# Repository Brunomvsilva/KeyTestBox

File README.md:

# KeytestBox

_Embedded platform designed to integrate automotive HMI key-testing systems in production environments._

_This project was developed at Preh Portugal as part of my Master’s thesis._

---

## Preview

<table align="center">
  <tr>
    <td align="center">
      <br>
      <em>Real KeytestBox Image</em>
    </td>
    <td align="center">
      <br>
      <em>3D model of the KeyTestBox enclosure</em>
    </td>
  </tr>
</table>

---

## Table of Contents

- [Introduction](#introduction)
- [Typical Key Test Output](#typical-key-test-output)
- [Incremental vs Continuous Tests](#incremental-vs-continuous-tests)
  - [Incremental Tests](#incremental-tests)
  - [Continuous Tests](#continuous-tests)
- [Problem Statement](#problem-statement)
  - [Problem 1: Delay via CAN/LIN](#problem-1-delay-when-reading-uut-data-via-can-or-lin)
  - [Problem 2: Low resolution and missed events](#problem-2-low-resolution-and-missed-events-in-incremental-tests)
  - [Consequence](#consequence-forced-to-use-expensive-continuous-test-systems)
- [Solution, Main Goals and Requirements](#solution-main-goals-and-requirements)
  - [Main Goals](#main-goals)
  - [Hardware Requirements](#hardware-requirements)
  - [Software Requirements](#software-requirements)
- [Hardware Overview](#hardware-overview)
- [Final Hardware](#final-hardware)
- [Software and Tools Used](#software-and-tools-used)
- [MQTT Commands Implemented](#mqtt-commands-implemented)
- [Tests and Results](#tests-and-results)
  - [UUT Lever and Testbench Setup](#uut-lever-test-and-testbench-setup)
  - [Sampling and Performance](#sampling-and-performance)
- [Conclusion](#conclusion)
- [Skills Learned](#skills-learned)

---

## Introduction 

Automotive HMI, such as climate and central control panels, rely on high-quality tactile feedback. **Force–displacement** key tests quantify that feel essencially by measuring the relation between **applied force** and **key travel**.

Images below display the **main components** of a key test system

<div align="center">
<table>
  <tr>
    <td style="padding-right: 40px;">
      
    </td>
    <td style="padding-left: 40px;">
      
    </td>
  </tr>
</table>
</div>

### During a test:
- The key is pressed by a **SMAC linear motor**  
- **Force** is measured using a **load cell with an amplifier**  
- **Key travel (displacement)** is obtained from the **SMAC internal encoder**  
- The **Unit Under Test (UUT)** sends data via **CAN/LIN** during the test, such as:  
  - **Key state (pressed / released)**
  - **Lever position or angle** (e.g. gear selector tests)  
  - **Selected gear value**  
  - **UUT Hall sensors or internal position data**  
  - Other diagnostic or status information

### Typical Key Test Output

The **Force–Displacement** curve is the most common way to characterize how a key or button behaves when it is pressed and released. It represents the force applied to the key as a function of its travel (displacement).

Curves differ depending on the type of key being tested.
During a test, the key is pressed (force increases) until it reaches a maximum point, and then released. From this curve, mechanical parameters of the key can be extracted:

| Symbol | Description |
|--------|-------------|
| **S1** | Displacement at which the key actuates (snap/collapse point). |
| **F1** | Actuation force – force required to trigger the snap of the membrane or key mechanism at S1. |
| **S2** | Displacement where electrical contact occurs with the PCB. |
| **F2** | Contact force – minimum force required to close the electrical contact at S2. |
| **F3** | Return force – force at which the electrical contact is released during the return movement. |
| **F4** | Force difference between actuation and release states. |
| **F5** | Maximum applied force during the test (should not exceed mechanical limits). |
| **Ss** | Maximum travel / end of mechanical stroke. |

One of the most important metrics derived from this curve is the **Snap Ratio (SR)**, which indicates how strong the tactile feedback is:

$$
SR=\dfrac{F_1-F_2}{F_1}\times 100\%
$$

- A higher **Snap Ratio** = stronger tactile feedback (more noticeable “click”).
- A lower **Snap Ratio** = softer feedback, which may feel smoother but less perceptible.
- Ideal **SR** values depend on the application.

---

## Incremental vs Continuous Tests

The flowcharts below provide a simplified comparison between the two testing methods.  
The main difference is that in **Incremental Tests**, the actuator stops at each step to acquire a sample, while in **Continuous Tests**, the actuator moves without stopping and data is sampled in real time.

<table align="center">
  <tr>
    <td align="center">
      <br>
      <em>Incremental Test Flowchart</em>
    </td>
    <td align="center">
      <br>
      <em>Continuous Test Flowchart</em>
    </td>
  </tr>
</table>

---

## Incremental Tests

### Incremental Test System Example (without the KeyTestBox)

- **Force** data is acquired by the host PC via a USB Data Acquisition (DAQ) device from National Instruments.
- **Position** data is acquired by RS232 from the actuator controller
- **Key State or info** data is acquired through a CAN/LIN-USB converter

### Advantages:
- Low cost
- Easier to implement

### Disadvantages
- **low test resolution** (low sample density)
- May miss the sampling of the **snap point**, especially on **short-travel keys**
- Can fail to meet client requirements

### Incremental Test Output Example

---

## Continuous Tests

### Continuous Test System (Without KeyTestBox)

In continuous testing, the actuator **moves without stopping**, and all signals are sampled in real time. This enables a smoother force–displacement curve and higher data accuracy.

- **Force** is measured by a load cell and continuously acquired via the DAQ system  
- **Position (travel)** is obtained from the SMAC actuator encoder in real time  
- The **Unit Under Test (UUT)** transmits its state (CAN/LIN), such as key/lever status or sensor values, during movement  
- All data is timestamped and saved by the DAQ system for later processing  

> While this setup delivers high accuracy and resolution, it uses sophisticated hardware and is **significantly more expensive**.

### Advantages
- **High sample density** → more precise force–travel curve  
- **Accurate snap detection**  
- **Faster test execution** → important in industrial production environments  

### Disadvantages
- **Substantially higher cost** due to DAQ modules and synchronization hardware.

### Continuous Test Output Example

---

## Problem Statement

In industrial test setups, especially for testing mechanical keys, the most common approach is the **incremental test method**. This approach is simple and cost-effective, and it can work well in many cases.

However, **in several real-world situations, incremental testing is not sufficient or may not work at all**. These limitations arise due to the way the test equipment communicates and the type of measurements required:

---

### Problem 1: Delay when reading UUT data via CAN or LIN

Many devices under test (UUTs) only report their internal state (e.g., whether a button is pressed or not) when the host explicitly **requests the data** using a communication protocol like **CAN** or **LIN**. This process introduces a delay between the request and the response.

If the actuator is moving during this time (as in a continuous test), by the time the host receives the data, the key is already in a **different position**, and the measured force has also changed. This causes a mismatch between the **key state**, **position**, and **force**, making the data unreliable.

---

### Problem 2: Low resolution and missed events in incremental tests

Given the problem 1, a good solution would be to **stop the actuator** and only then **request the data via CAN or LIN**, then wait for the response.  
However, as said before, **incremental testing has limited resolution**. Since the actuator only samples at discrete steps, fast or short events — such as the **snap point** (a sudden change in force when pressing a key) — may occur between two sample points and go undetected.

This is particularly problematic for **short-travel keys**, where the full keypress happens in a very small movement range. In such cases, a small number of samples is not enough to capture the key’s behavior accurately.

---

### Consequence: Forced to use expensive continuous test systems

To solve these problems, test stations often switch to **continuous testing**, which are significantly more expensive

---

## Solution, Main Goals and Requirements

To overcome the limitations of incremental testing and avoid the high cost of commercial continuous testing systems, a new solution is required — one that enables **real-time, synchronized testing** without the complexity and price of traditional DAQ systems.

The **KeyTestBox** is proposed as a **low-cost**, **modular**, and **reusable** platform suitable for production testing environments.

### Main Goals 

- **Real-time acquisition** of:
  - **Force** (via load cell)
  - **Position** (via SMAC encoder)
  - **UUT data** (via CAN or LIN protocols)

### Hardware Requirements

- 24 VDC power supply  
- CAN interface (supports baud rate up to 1 Mbps)  
- LIN interface (supports baud rate up to 19 200 bps)  
- Ethernet port (10/100 Mbps)  
- Two RS232 interfaces  
- Minimum of five differential analog inputs (−10 V to +10 V) **(Mainly to read the 2 Load Cells but some extra were added)**  
- Two linear encoder counters  
- Microcontroller-based system
- PCB design

---

### Software Requirements

- Firmware developed in C
- Start and stop a test routine upon request  
- Ability to export the acquired test data  
- Capability to execute external commands during the test routine  
- Use of the MQTT protocol for communication with the host  

---

## Hardware Overview

---

## Final Hardware

[Full **Hardware Schematic**](PCB/keytestbox_schematic.pdf)

### Main Components

- STM32F767VIT6
- LAN8742A
- 2x MAX1032 (ADC)
- MCP2021 (LIN)
- MCP2551 (CAN)
- MAX232 (RS232 Converter) 
- STLINK-V3 Debugger SWD
 
<table align="center">
  <tr>
    <td align="center">
      <br>
      <em>Real KeytestBox Image</em>
    </td>
    <td align="center">
      <br>
      <em>3D model of the KeyTestBox enclosure</em>
    </td>
  </tr>
</table>

> PCB Schematic done by me in KiCad
> PCB Layout was designed by another company
---

## Software and Tools used

- STM32Cube IDE
- FreeRTOS
- LwIP IP Stack
- Mosquitto MQTT
- Percepio Tracealyzer

---

## MQTT Commands Implemented

---

## Tests and Results

The primary test target was a **gear shift lever** from the UUT shown below. This lever represents one of the most challenging components to test due to several factors:

- The lever travel is **approximately 12 mm**, much longer than typical pushbuttons (≈ 3 mm).
- Each test cycle includes **two snap events** in each direction (forward and return).
- The UUT transmits a **high volume of CAN data** during movement, requiring reliable high-frequency acquisition and synchronization.

### UUT Lever Test and Testbench Setup

The figure highlights the tested lever in red and shows the complete testbench used.

---

### Sampling and Performance

Tests were conducted at various sampling frequencies. The system successfully performed synchronized data acquisition at rates **up to 3000 Hz**, capturing:

- **Force data** via load cell  
- **Position data** from the SMAC actuator encoder  
- **Key state data** via CAN from the UUT

This sampling rate proved sufficient for accurate detection of all snap points and detailed force-position profiles.

> Increasing the frequency beyond 3000 Hz was not necessary and led to **excessive data**, which becomes impractical to store locally due to **RAM constraints**.

### Test Result Graph @3000Hz + Lever Position 

### Test Result Graph @1250Hz + Gear Selected

---

## Conclusion

All the defined requirements were met.
Furthermore, the tests demonstrated that the KeyTestBox platform is fully capable of performing continuous key testing with:

- High-resolution data acquisition up to **3000 Hz**
- Data synchronization
- Successful operation even on demanding UUT test cases

> The **KeyTestBox achieved a cost reduction of approximately 91.75%**, lowering the price about 12 times comparing to the other solution

> One limitation was the available RAM, which is sufficient for most use cases. However, for UUTs that transmit **large volumes of CAN data**, it may be necessary to **select only the relevant CAN/LIN UUT data** to avoid memory overflow.  
>  
> If full data capture is required, this limitation can easily be addressed by using a **microcontroller with more RAM**, for example STM32H7 family.

---

## Skills Learned

This project provided practical experience in the design and implementation of a **cyber-physical embedded system** for industrial testing applications.

### General Skills
- **Real-Time Embedded Systems**
- **Cyber-Physical System Design**  
- **Signal and Data Acquisition**
- **Cost–Performance Trade-Offs**

### Technical Skills
- **Embedded C (STM32)**
- **FreeRTOS task design**
- **Peripheral integration** — SPI, UART, ADC, CAN, LIN, Encoders, Timers
- **Networking with LwIP + MQTT**
- **PCB schematic design (KiCad)**

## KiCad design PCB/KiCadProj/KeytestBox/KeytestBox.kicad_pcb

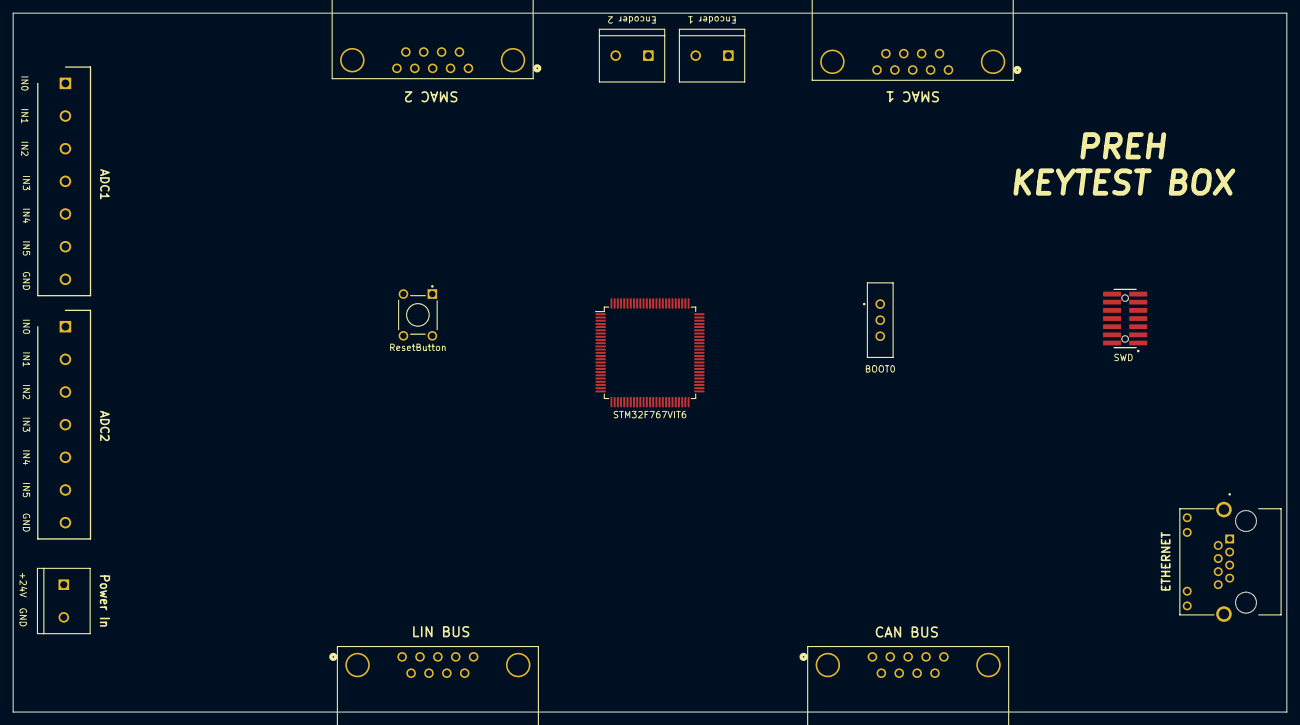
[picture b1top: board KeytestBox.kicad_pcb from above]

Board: 2 copper layers, 198.1 x 108.7 mm, 14 parts (0 on the bottom side), 13 nets, no tracks yet.

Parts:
J1: Conn_02x07_Odd_Even; SAMTEC_FTSH-107-01-L-DV-K-A
J2, J11, J12: Screw_Terminal_01x02; TE_282837-2
J3: SCREW_TERM_1x7; SHDR7W100P0X508_1X7_3556X820X1000P
J4: RJHSE-5384; AMPHENOL_RJHSE-5384
J5, J6, J7, J8: DB9; CONN9X1_2286550-1_TEC
J9: Screw_Terminal_01x07; SHDR7W100P0X508_1X7_3556X820X1000P
SW1: SW_SPDT; SW_EG1218
SW2: ResetButton; SW_1825910-6-4
U1: STM32F767VIT6; LQFP-100_14x14mm_P0.5mm

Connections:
+24V: J2.1, J8.9
ENC1_CH1: J11.1, U1.63 (PC6)
ENC1_CH2: J11.2, U1.64 (PC7)
ENC2_CH1: J12.1, U1.59 (PD12)
ENC2_CH2: J12.2, U1.60 (PD13)
GND: J1.11, J2.2, J3.7, J5.5, J6.5, J7.3, J7.6, J8.5, J8.6, J9.7, SW1.3 (C), SW2.3 (K), SW2.4 (A), U1.10 (VSS), U1.19 (VSSA), U1.26 (VSS), U1.49 (VSS), U1.74 (VSS), U1.99 (VSS)
GNDPWR: J4.S1 (SHIELD1/SHIELD2), J4.S2 (SHIELD)
NRST: J1.12, SW2.1, SW2.2, U1.14 (NRST)
unnamed: J4.4 (NC), J4.5 (NC)
unnamed: J4.7 (NC), J4.8 (NC)
SD1_out: SW1.1 (A), U1.6 (VBAT), U1.11 (VDD), U1.20 (VREF+), U1.27 (VDD), U1.50 (VDD), U1.75 (VDD), U1.100 (VDD)
VCP_RX: J1.13, U1.69 (PA10)
VCP_TX: J1.14, U1.68 (PA9)

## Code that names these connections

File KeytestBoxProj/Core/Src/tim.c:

/* USER CODE BEGIN Header */
/**
  ******************************************************************************
  * @file    tim.c
  * @brief   This file provides code for the configuration
  *          of the TIM instances.
  ******************************************************************************
  * @attention
  *
  * Copyright (c) 2023 STMicroelectronics.
  * All rights reserved.
  *
  * This software is licensed under terms that can be found in the LICENSE file
  * in the root directory of this software component.
  * If no LICENSE file comes with this software, it is provided AS-IS.
  *
  ******************************************************************************
  */
/* USER CODE END Header */
/* Includes ------------------------------------------------------------------*/
#include "tim.h"

/* USER CODE BEGIN 0 */

/* USER CODE END 0 */

TIM_HandleTypeDef htim3;
TIM_HandleTypeDef htim4;
TIM_HandleTypeDef htim13;
TIM_HandleTypeDef htim14;

/* TIM3 init function */
void MX_TIM3_Init(void)
{

  /* USER CODE BEGIN TIM3_Init 0 */

  /* USER CODE END TIM3_Init 0 */

  TIM_Encoder_InitTypeDef sConfig = {0};
  TIM_MasterConfigTypeDef sMasterConfig = {0};

  /* USER CODE BEGIN TIM3_Init 1 */

  /* USER CODE END TIM3_Init 1 */
  htim3.Instance = TIM3;
  htim3.Init.Prescaler = 0;
  htim3.Init.CounterMode = TIM_COUNTERMODE_UP;
  htim3.Init.Period = 65535;
  htim3.Init.ClockDivision = TIM_CLOCKDIVISION_DIV1;
  htim3.Init.AutoReloadPreload = TIM_AUTORELOAD_PRELOAD_ENABLE;
  sConfig.EncoderMode = TIM_ENCODERMODE_TI12;
  sConfig.IC1Polarity = TIM_ICPOLARITY_RISING;
  sConfig.IC1Selection = TIM_ICSELECTION_DIRECTTI;
  sConfig.IC1Prescaler = TIM_ICPSC_DIV1;
  sConfig.IC1Filter = 10;
  sConfig.IC2Polarity = TIM_ICPOLARITY_RISING;
  sConfig.IC2Selection = TIM_ICSELECTION_DIRECTTI;
  sConfig.IC2Prescaler = TIM_ICPSC_DIV1;
  sConfig.IC2Filter = 10;
  if (HAL_TIM_Encoder_Init(&htim3, &sConfig) != HAL_OK)
  {
    Error_Handler();
  }
  sMasterConfig.MasterOutputTrigger = TIM_TRGO_RESET;
  sMasterConfig.MasterSlaveMode = TIM_MASTERSLAVEMODE_DISABLE;
  if (HAL_TIMEx_MasterConfigSynchronization(&htim3, &sMasterConfig) != HAL_OK)
  {
    Error_Handler();
  }
  /* USER CODE BEGIN TIM3_Init 2 */

  /* USER CODE END TIM3_Init 2 */

}
/* TIM4 init function */
void MX_TIM4_Init(void)
{

  /* USER CODE BEGIN TIM4_Init 0 */

  /* USER CODE END TIM4_Init 0 */

  TIM_Encoder_InitTypeDef sConfig = {0};
  TIM_MasterConfigTypeDef sMasterConfig = {0};

  /* USER CODE BEGIN TIM4_Init 1 */

  /* USER CODE END TIM4_Init 1 */
  htim4.Instance = TIM4;
  htim4.Init.Prescaler = 0;
  htim4.Init.CounterMode = TIM_COUNTERMODE_UP;
  htim4.Init.Period = 65535;
  htim4.Init.ClockDivision = TIM_CLOCKDIVISION_DIV1;
  htim4.Init.AutoReloadPreload = TIM_AUTORELOAD_PRELOAD_ENABLE;
  sConfig.EncoderMode = TIM_ENCODERMODE_TI12;
  sConfig.IC1Polarity = TIM_ICPOLARITY_RISING;
  sConfig.IC1Selection = TIM_ICSELECTION_DIRECTTI;
  sConfig.IC1Prescaler = TIM_ICPSC_DIV1;
  sConfig.IC1Filter = 10;
  sConfig.IC2Polarity = TIM_ICPOLARITY_RISING;
  sConfig.IC2Selection = TIM_ICSELECTION_DIRECTTI;
  sConfig.IC2Prescaler = TIM_ICPSC_DIV1;
  sConfig.IC2Filter = 10;
  if (HAL_TIM_Encoder_Init(&htim4, &sConfig) != HAL_OK)
  {
    Error_Handler();
  }
  sMasterConfig.MasterOutputTrigger = TIM_TRGO_RESET;
  sMasterConfig.MasterSlaveMode = TIM_MASTERSLAVEMODE_DISABLE;
  if (HAL_TIMEx_MasterConfigSynchronization(&htim4, &sMasterConfig) != HAL_OK)
  {
    Error_Handler();
  }
  /* USER CODE BEGIN TIM4_Init 2 */

  /* USER CODE END TIM4_Init 2 */

}
/* TIM13 init function */
void MX_TIM13_Init(void)
{

  /* USER CODE BEGIN TIM13_Init 0 */

  /* USER CODE END TIM13_Init 0 */

  /* USER CODE BEGIN TIM13_Init 1 */

  /* USER CODE END TIM13_Init 1 */
  htim13.Instance = TIM13;
  htim13.Init.Prescaler = 0;
  htim13.Init.CounterMode = TIM_COUNTERMODE_UP;
  htim13.Init.Period = 64799;
  htim13.Init.ClockDivision = TIM_CLOCKDIVISION_DIV1;
  htim13.Init.AutoReloadPreload = TIM_AUTORELOAD_PRELOAD_ENABLE;
  if (HAL_TIM_Base_Init(&htim13) != HAL_OK)
  {
    Error_Handler();
  }
  /* USER CODE BEGIN TIM13_Init 2 */

  /* USER CODE END TIM13_Init 2 */

}
/* TIM14 init function */
void MX_TIM14_Init(void)
{

  /* USER CODE BEGIN TIM14_Init 0 */

  /* USER CODE END TIM14_Init 0 */

  /* USER CODE BEGIN TIM14_Init 1 */

  /* USER CODE END TIM14_Init 1 */
  htim14.Instance = TIM14;
  htim14.Init.Prescaler = 0;
  htim14.Init.CounterMode = TIM_COUNTERMODE_UP;
  htim14.Init.Period = 65535;
  htim14.Init.ClockDivision = TIM_CLOCKDIVISION_DIV1;
  htim14.Init.AutoReloadPreload = TIM_AUTORELOAD_PRELOAD_DISABLE;
  if (HAL_TIM_Base_Init(&htim14) != HAL_OK)
  {
    Error_Handler();
  }
  /* USER CODE BEGIN TIM14_Init 2 */

  /* USER CODE END TIM14_Init 2 */

}

void HAL_TIM_Encoder_MspInit(TIM_HandleTypeDef* tim_encoderHandle)
{

  GPIO_InitTypeDef GPIO_InitStruct = {0};
  if(tim_encoderHandle->Instance==TIM3)
  {
  /* USER CODE BEGIN TIM3_MspInit 0 */

  /* USER CODE END TIM3_MspInit 0 */
    /* TIM3 clock enable */
    __HAL_RCC_TIM3_CLK_ENABLE();

    __HAL_RCC_GPIOC_CLK_ENABLE();
    /**TIM3 GPIO Configuration
    PC6     ------> TIM3_CH1
    PC7     ------> TIM3_CH2
    */
    GPIO_InitStruct.Pin = ENC2_CH1_Pin|ENC2_CH2_Pin;
    GPIO_InitStruct.Mode = GPIO_MODE_AF_PP;
    GPIO_InitStruct.Pull = GPIO_NOPULL;
    GPIO_InitStruct.Speed = GPIO_SPEED_FREQ_LOW;
    GPIO_InitStruct.Alternate = GPIO_AF2_TIM3;
    HAL_GPIO_Init(GPIOC, &GPIO_InitStruct);

  /* USER CODE BEGIN TIM3_MspInit 1 */

  /* USER CODE END TIM3_MspInit 1 */
  }
  else if(tim_encoderHandle->Instance==TIM4)
  {
  /* USER CODE BEGIN TIM4_MspInit 0 */

  /* USER CODE END TIM4_MspInit 0 */
    /* TIM4 clock enable */
    __HAL_RCC_TIM4_CLK_ENABLE();

    __HAL_RCC_GPIOD_CLK_ENABLE();
    /**TIM4 GPIO Configuration
    PD12     ------> TIM4_CH1
    PD13     ------> TIM4_CH2
    */
    GPIO_InitStruct.Pin = ENC1_CH1_Pin|ENC1_CH2_Pin;
    GPIO_InitStruct.Mode = GPIO_MODE_AF_PP;
    GPIO_InitStruct.Pull = GPIO_NOPULL;
    GPIO_InitStruct.Speed = GPIO_SPEED_FREQ_LOW;
    GPIO_InitStruct.Alternate = GPIO_AF2_TIM4;
    HAL_GPIO_Init(GPIOD, &GPIO_InitStruct);

  /* USER CODE BEGIN TIM4_MspInit 1 */

  /* USER CODE END TIM4_MspInit 1 */
  }
}

void HAL_TIM_Base_MspInit(TIM_HandleTypeDef* tim_baseHandle)
{

  if(tim_baseHandle->Instance==TIM13)
  {
  /* USER CODE BEGIN TIM13_MspInit 0 */

  /* USER CODE END TIM13_MspInit 0 */
    /* TIM13 clock enable */
    __HAL_RCC_TIM13_CLK_ENABLE();

    /* TIM13 interrupt Init */
    HAL_NVIC_SetPriority(TIM8_UP_TIM13_IRQn, 5, 0);
    HAL_NVIC_EnableIRQ(TIM8_UP_TIM13_IRQn);
  /* USER CODE BEGIN TIM13_MspInit 1 */

  /* USER CODE END TIM13_MspInit 1 */
  }
  else if(tim_baseHandle->Instance==TIM14)
  {
  /* USER CODE BEGIN TIM14_MspInit 0 */

  /* USER CODE END TIM14_MspInit 0 */
    /* TIM14 clock enable */
    __HAL_RCC_TIM14_CLK_ENABLE();
  /* USER CODE BEGIN TIM14_MspInit 1 */

  /* USER CODE END TIM14_MspInit 1 */
  }
}

void HAL_TIM_Encoder_MspDeInit(TIM_HandleTypeDef* tim_encoderHandle)
{

  if(tim_encoderHandle->Instance==TIM3)
  {
  /* USER CODE BEGIN TIM3_MspDeInit 0 */

  /* USER CODE END TIM3_MspDeInit 0 */
    /* Peripheral clock disable */
    __HAL_RCC_TIM3_CLK_DISABLE();

    /**TIM3 GPIO Configuration
    PC6     ------> TIM3_CH1
    PC7     ------> TIM3_CH2
    */
    HAL_GPIO_DeInit(GPIOC, ENC2_CH1_Pin|ENC2_CH2_Pin);

  /* USER CODE BEGIN TIM3_MspDeInit 1 */

  /* USER CODE END TIM3_MspDeInit 1 */
  }
  else if(tim_encoderHandle->Instance==TIM4)
  {
  /* USER CODE BEGIN TIM4_MspDeInit 0 */

  /* USER CODE END TIM4_MspDeInit 0 */
    /* Peripheral clock disable */
    __HAL_RCC_TIM4_CLK_DISABLE();

    /**TIM4 GPIO Configuration
    PD12     ------> TIM4_CH1
    PD13     ------> TIM4_CH2
    */
    HAL_GPIO_DeInit(GPIOD, ENC1_CH1_Pin|ENC1_CH2_Pin);

  /* USER CODE BEGIN TIM4_MspDeInit 1 */

  /* USER CODE END TIM4_MspDeInit 1 */
  }
}

void HAL_TIM_Base_MspDeInit(TIM_HandleTypeDef* tim_baseHandle)
{

  if(tim_baseHandle->Instance==TIM13)
  {
  /* USER CODE BEGIN TIM13_MspDeInit 0 */

  /* USER CODE END TIM13_MspDeInit 0 */
    /* Peripheral clock disable */
    __HAL_RCC_TIM13_CLK_DISABLE();

    /* TIM13 interrupt Deinit */
    HAL_NVIC_DisableIRQ(TIM8_UP_TIM13_IRQn);
  /* USER CODE BEGIN TIM13_MspDeInit 1 */

  /* USER CODE END TIM13_MspDeInit 1 */
  }
  else if(tim_baseHandle->Instance==TIM14)
  {
  /* USER CODE BEGIN TIM14_MspDeInit 0 */

  /* USER CODE END TIM14_MspDeInit 0 */
    /* Peripheral clock disable */
    __HAL_RCC_TIM14_CLK_DISABLE();
  /* USER CODE BEGIN TIM14_MspDeInit 1 */

  /* USER CODE END TIM14_MspDeInit 1 */
  }
}

/* USER CODE BEGIN 1 */

/* USER CODE END 1 */

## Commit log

2025-11-05 add project files
2025-11-06 add Images
2025-11-06 add img
2025-11-06 arranje image
2025-11-07 Refine README content for better clarity
    Updated README.md for clarity and detail improvements.
2025-11-08 Refactor README.md for clarity and structure
    Updated formatting and content structure in README.md, including section headings and clarifications on testing methods.
2025-11-08 add Image HardwareOverview
2025-11-08 Adjust image sizes and add MQTT commands section
    Updated image dimensions and added MQTT commands section.
2025-11-08 Update README to specify Hardware
2025-11-08 add Command Table img
2025-11-08 Update README with MQTT commands and test results
    Added section on MQTT commands and tests conducted on UUT lever.
2025-11-08 Revise test description for gear shift lever
    Updated the description of the primary test target and clarified the testing conditions and results.
2025-11-09 Update README with conclusion and skills learned
    Added conclusion and skills learned sections to README.
2025-11-09 Add table of contents to README.md
2025-11-09 Remove emoji from Table of Contents header
2025-11-09 Update README with protocol and memory details
    Clarified communication protocol and RAM limitations in the README.
2025-11-10 Correct section title in README.md
2025-11-10 Fix link in README for UUT Lever section
2025-11-19 Refine project description in README.md
2025-11-19 Format project description in README.md
2025-11-19 Fix formatting of project description in README
